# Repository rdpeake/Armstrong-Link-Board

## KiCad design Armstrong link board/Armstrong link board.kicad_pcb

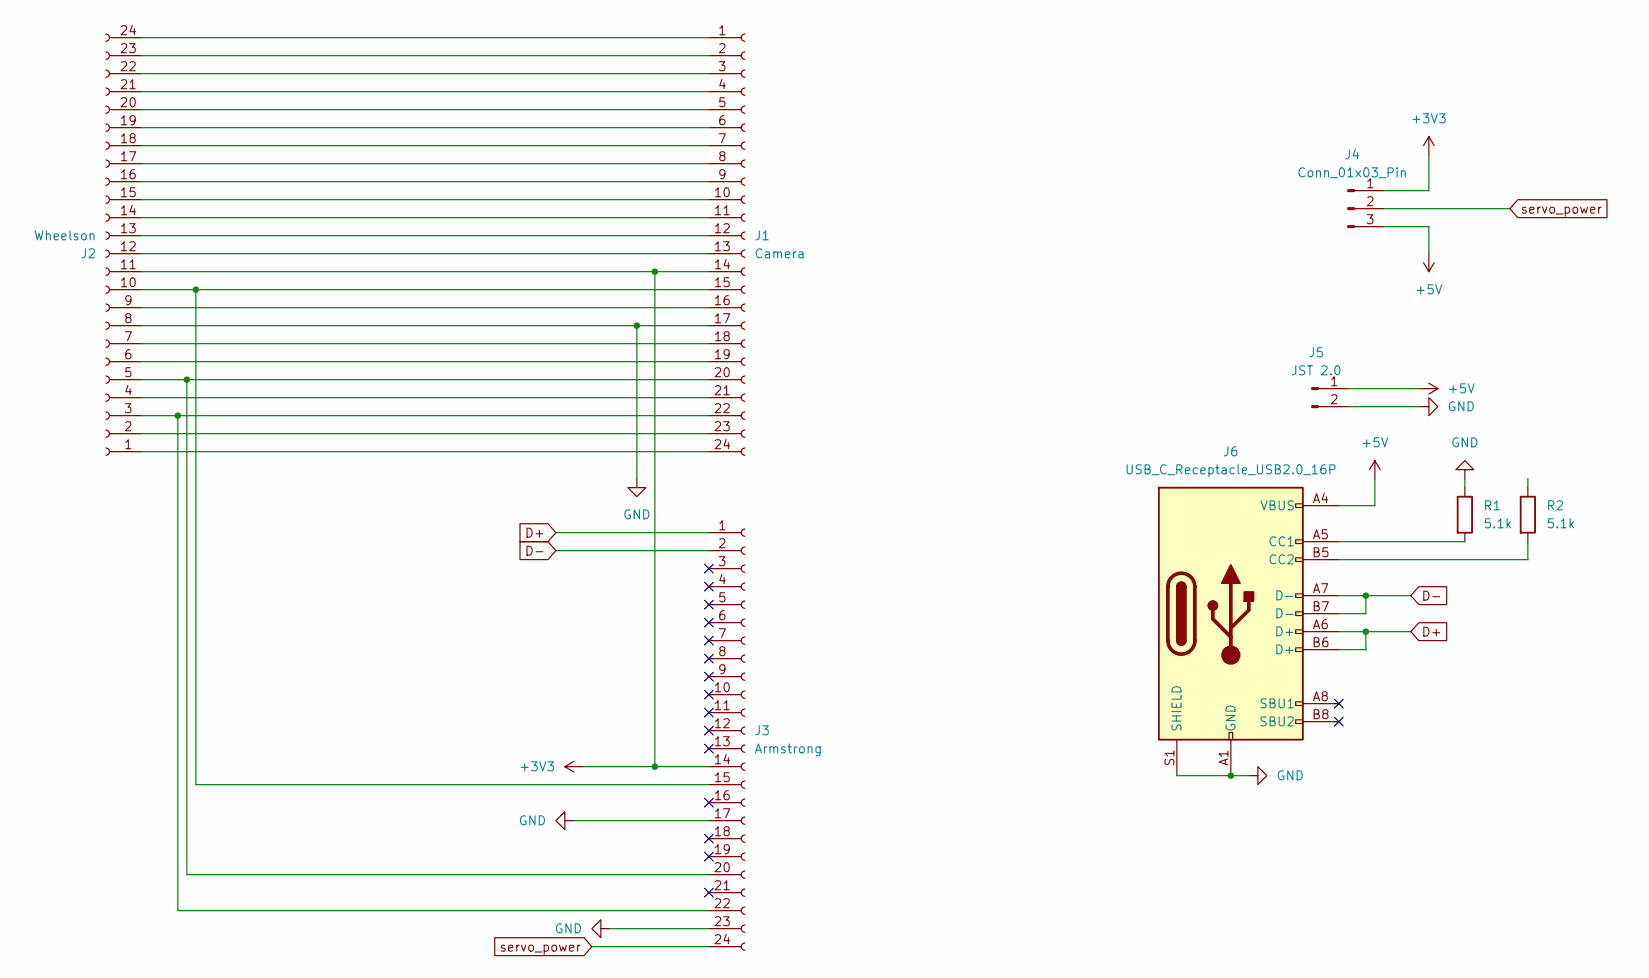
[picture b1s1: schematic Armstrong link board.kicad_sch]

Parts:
J1: Camera; Molex_502244-2430_1x24-1MP_P0.5mm_Horizontal
J2: Wheelson; Molex_502244-2430_1x24-1MP_P0.5mm_Horizontal
J3: Armstrong; Molex_502231-2400_1x24-1SH_P0.5mm_Vertical
J4: Conn_01x03_Pin; PinHeader_1x03_P2.54mm_Vertical_SMD_Pin1Left
J5: JST 2.0; JST_PH_S2B-PH-SM4-TB_1x02-1MP_P2.00mm_Horizontal
J6: USB_C_Receptacle_USB2.0_16P; USB_C_Receptacle_GCT_USB4105-xx-A_16P_TopMnt_Horizontal
R1, R2: 5.1k; R_0805_2012Metric

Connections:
+3V3: J1.14, J2.11, J3.14, J4.1
+5V: J4.3, J5.1, J6.A4 (VBUS), J6.A9 (VBUS), J6.B4 (VBUS), J6.B9 (VBUS)
D+: J3.1, J6.A6 (D+), J6.B6 (D+)
D-: J3.2, J6.A7 (D-), J6.B7 (D-)
GND: J1.17, J2.8, J3.17, J3.23, J5.2, J6.A1 (GND), J6.A12 (GND), J6.B1 (GND), J6.B12 (GND), J6.S1 (SHIELD), R1.1
unnamed: J1.1, J2.24
unnamed: J1.2, J2.23
unnamed: J1.3, J2.22
unnamed: J1.4, J2.21
unnamed: J1.5, J2.20
unnamed: J1.6, J2.19
unnamed: J1.7, J2.18
unnamed: J1.8, J2.17
unnamed: J1.9, J2.16
unnamed: J1.10, J2.15
unnamed: J1.11, J2.14
unnamed: J1.12, J2.13
unnamed: J1.13, J2.12
unnamed: J1.15, J2.10, J3.15
unnamed: J1.16, J2.9
unnamed: J1.18, J2.7
unnamed: J1.19, J2.6
unnamed: J1.20, J2.5, J3.20
unnamed: J1.21, J2.4
unnamed: J1.22, J2.3, J3.22
unnamed: J1.23, J2.2
unnamed: J1.24, J2.1
unnamed: J6.A5 (CC1), R1.2
unnamed: J6.B5 (CC2), R2.2
servo_power: J3.24, J4.2

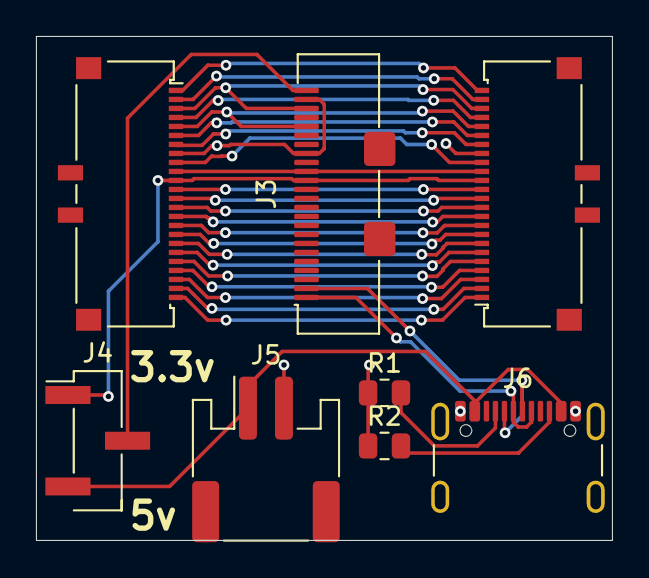
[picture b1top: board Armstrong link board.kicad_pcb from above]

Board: 2 copper layers, 32.0 x 28.0 mm, 8 parts (0 on the bottom side), 30 nets.

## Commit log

2025-02-01 create schematic and pcb
2025-02-21 connect ground and shield from usb
